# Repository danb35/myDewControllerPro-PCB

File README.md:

# myDewControllerPro-PCB
KiCad schematic and board for myDewControllerPro: https://sourceforge.net/projects/arduinonanodewcontrollerpro/

# Introduction
myFocuserPro is a DIY, Arduino-based dew heater controller designed for use with telescopes.  The design, source code, schematics, PCB files (Gerbers), and extensive documentation are available at the link above.  So what am I doing in this repo?

Unfortunately, the Gerbers there have a few issues, most notably that the footprint for the reverse-polarity protection diode (D1 on the schematic) just doesn't fit the specified diode.  The specified "fix" for the problem is to file down the leads of the diode until they fit through the holes.  And while this should be a trivial thing to fix, editable source files for the schematic and board haven't been released.

To address this, I re-drew the schematic and PCB layout in KiCad 6.0.  [KiCad](https://www.kicad.org/) is free, open source electronics design software, so you can download it to edit these files as desired.

# Design changes
This schematic is identical to the schematic at SourceForge.  I intend (and hope) that the schematic will be easier to read and follow, but there should not be any changes in the components or how they're connected.  Most of the reference designators (i.e., R3, C2, etc.) are identical, but KiCad has changed some of the semiconductors.  I have, however, made a few changes to the board layout.

First, of course, there's the change that drove the whole redesign--the footprint for D1 now actually fits the specified diode.  I've also replaced most of the places where pin headers had been used for off-board connections (e.g., for the pushbuttons, the display, etc.) with JST-XH connectors.  These provide some friction to prevent connections from coming loose inadvertently, and also polarize the connections (so, e.g., you can't plug in a LED backward).

# Bill of Materials
The bill of materials is not appreciably different from the upstream project, but it's now included in this repo, both as an OpenDocument Spreadsheet file and as a PDF.

# Enclosure
While the board size is similar to the original, it is not identical, and it will not fit in the 3D-printed case design that's posted on SourceForge.  I've designed an enclosure that will fit this board; STLs and STEP files are in the `Enclosure` directory.

# Board Images

# Ordering
I don't sell these boards; you can have them made by any PCB fab you choose.  To do so, simply download Gerber/myDewControllerPro.zip from this repo, upload it to your fab of choice, and have at it.  If you don't have a fab of choice, consider the two linked below, in which I have no financial interest (i.e., I'm not an affiliate, partner, or anything else; I don't make anything from your purchase of these boards--I'm just a customer of both services).

To order from JLCPCB, or most other PCB fabs, download the .zip file from the `Gerbers` directory.  You can then upload it to your preferred vendor to price and order your PCBs.

## OSHPark
OSHPark are an American company known for high-quality boards.  They'll produce three copies of your design for $5 per square inch, in purple, with gold plating.  This cost is often higher than the Chinese fabs, but they don't charge shipping, and you don't have to wait for shipping for China.  This board costs about $62 shipped for three copies as of this writing.  You can order boards using this link:
https://oshpark.com/profiles/danb35

## JLCPCB
[JLCPCB](https://jlcpcb.com/) are a Chinese PCB fab that I've been pretty happy with.  Their prices are low (starting at $2/5 boards), they produce the boards quickly, and they ship quickly via DHL.  The biggest drawback is the cost of shipping--at this writing, five boards will cost you $2, but the shipping is another $20 or more.

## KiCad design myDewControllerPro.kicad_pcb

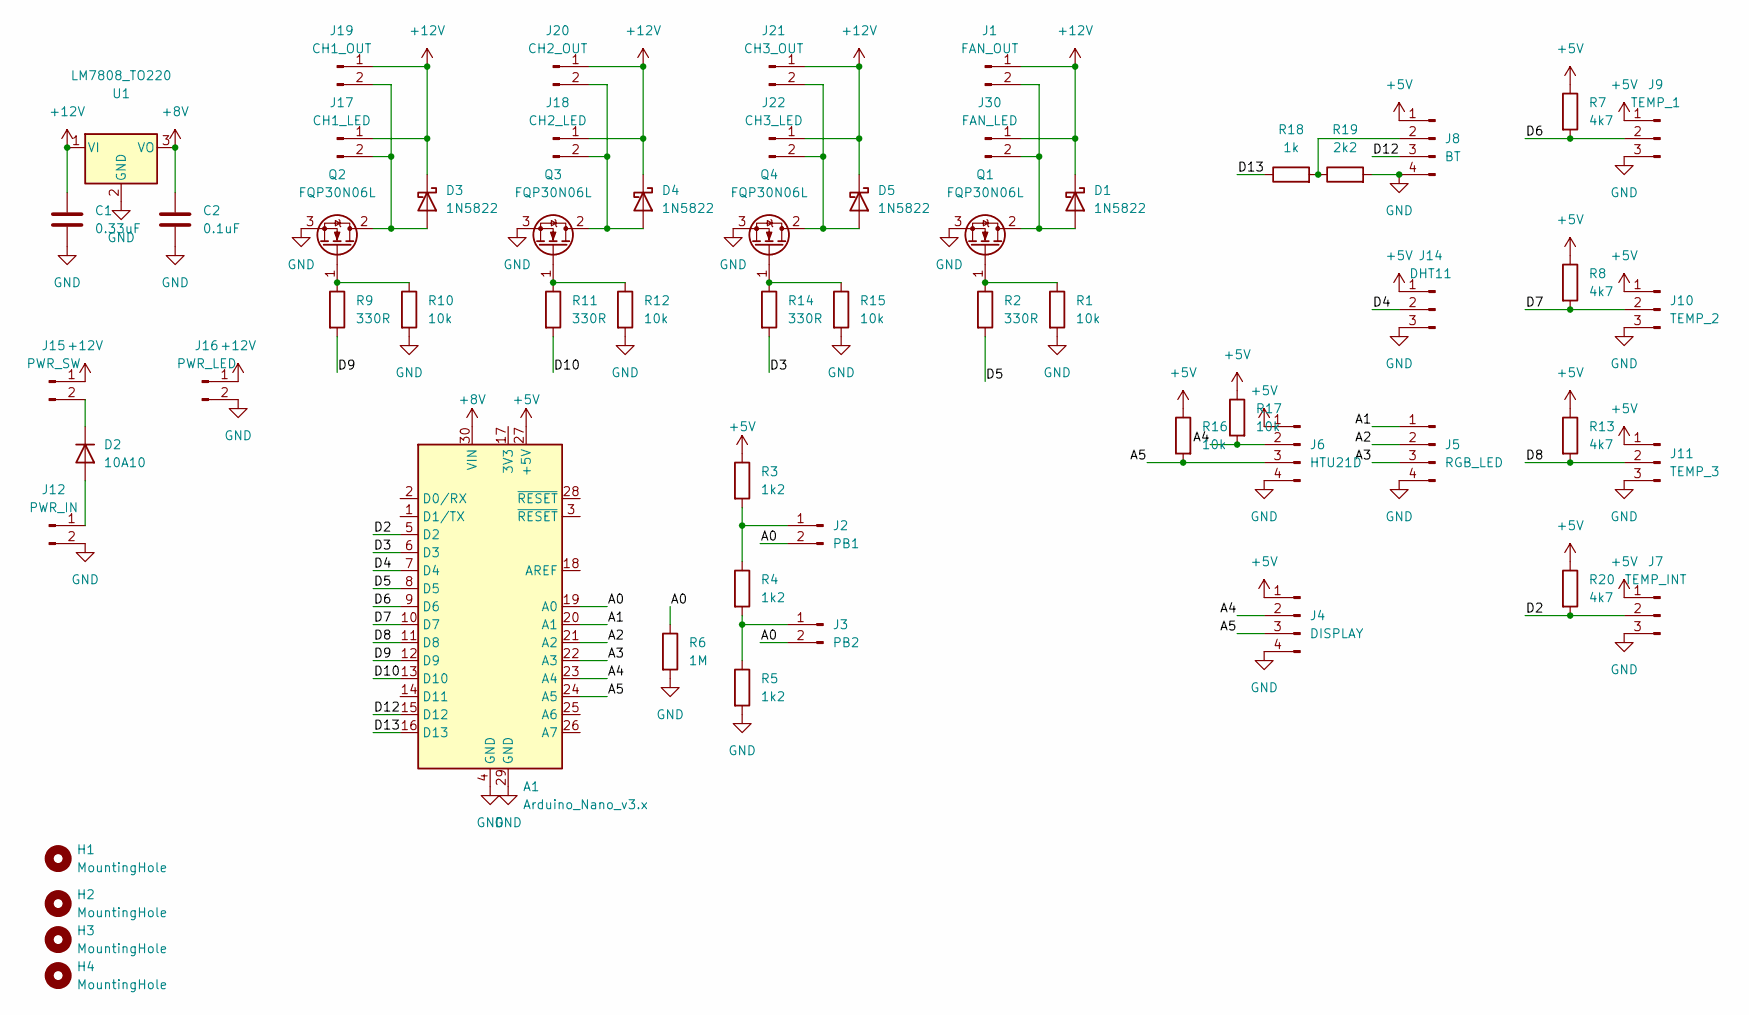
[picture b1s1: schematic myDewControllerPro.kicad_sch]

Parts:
A1: Arduino_Nano_v3.x; Arduino_Nano
C1: 0.33uF; C_Disc_D6.0mm_W4.4mm_P5.00mm
C2: 0.1uF; C_Disc_D6.0mm_W4.4mm_P5.00mm
D1, D3, D4, D5: 1N5822; D_DO-201AD_P15.24mm_Horizontal
D2: 10A10
H1, H2, H3, H4: MountingHole; MountingHole_3.2mm_M3
J1: FAN_OUT; JST_XH_B2B-XH-A_1x02_P2.50mm_Vertical
J2: PB1; JST_XH_B2B-XH-A_1x02_P2.50mm_Vertical
J3: PB2; JST_XH_B2B-XH-A_1x02_P2.50mm_Vertical
J4: DISPLAY; JST_XH_B4B-XH-A_1x04_P2.50mm_Vertical
J5: RGB_LED; JST_XH_B4B-XH-A_1x04_P2.50mm_Vertical
J6: HTU21D; JST_XH_B4B-XH-A_1x04_P2.50mm_Vertical
J7: TEMP_INT; JST_XH_B3B-XH-A_1x03_P2.50mm_Vertical
J8: BT; PinHeader_1x04_P2.54mm_Vertical
J9: TEMP_1; JST_XH_B3B-XH-A_1x03_P2.50mm_Vertical
J10: TEMP_2; JST_XH_B3B-XH-A_1x03_P2.50mm_Vertical
J11: TEMP_3; JST_XH_B3B-XH-A_1x03_P2.50mm_Vertical
J12: PWR_IN; JST_XH_B2B-XH-A_1x02_P2.50mm_Vertical
J14: DHT11; JST_XH_B3B-XH-AM_1x03_P2.50mm_Vertical
J15: PWR_SW; JST_XH_B2B-XH-A_1x02_P2.50mm_Vertical
J16: PWR_LED; JST_XH_B2B-XH-A_1x02_P2.50mm_Vertical
J17: CH1_LED; JST_XH_B2B-XH-A_1x02_P2.50mm_Vertical
J18: CH2_LED; JST_XH_B2B-XH-A_1x02_P2.50mm_Vertical
J19: CH1_OUT; JST_XH_B2B-XH-A_1x02_P2.50mm_Vertical
J20: CH2_OUT; JST_XH_B2B-XH-A_1x02_P2.50mm_Vertical
J21: CH3_OUT; JST_XH_B2B-XH-A_1x02_P2.50mm_Vertical
J22: CH3_LED; JST_XH_B2B-XH-A_1x02_P2.50mm_Vertical
J30: FAN_LED; JST_XH_B2B-XH-A_1x02_P2.50mm_Vertical
Q1, Q2, Q3, Q4: FQP30N06L; TO-220-3_Vertical
R1, R10, R12, R15, R16, R17: 10k; R_Axial_DIN0309_L9.0mm_D3.2mm_P5.08mm_Vertical
R2, R9, R11, R14: 330R; R_Axial_DIN0309_L9.0mm_D3.2mm_P5.08mm_Vertical
R3, R4, R5: 1k2; R_Axial_DIN0309_L9.0mm_D3.2mm_P5.08mm_Vertical
R6: 1M; R_Axial_DIN0309_L9.0mm_D3.2mm_P5.08mm_Vertical
R7, R8, R13, R20: 4k7; R_Axial_DIN0309_L9.0mm_D3.2mm_P5.08mm_Vertical
R18: 1k; R_Axial_DIN0309_L9.0mm_D3.2mm_P5.08mm_Vertical
R19: 2k2; R_Axial_DIN0309_L9.0mm_D3.2mm_P5.08mm_Vertical
U1: LM7808_TO220; TO-220-3_Vertical

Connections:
+5V: A1.27 (+5V), J4.1, J6.1, J7.1, J8.1, J9.1, J10.1, J11.1, J14.1, R3.1, R7.1, R8.1, R13.1, R16.1, R17.1, R20.1
+8V: A1.30 (VIN), C2.1, U1.3 (VO)
+12V: C1.1, D1.1 (K), D3.1 (K), D4.1 (K), D5.1 (K), J1.1, J15.1, J16.1, J17.1, J18.1, J19.1, J20.1, J21.1, J22.1, J30.1, U1.1 (VI)
/A0: A1.19 (A0), J2.2, J3.2, R6.1
/A1: A1.20 (A1), J5.1
/A2: A1.21 (A2), J5.2
/A3: A1.22 (A3), J5.3
/A4: A1.23 (A4), J4.2, J6.2, R17.2
/A5: A1.24 (A5), J4.3, J6.3, R16.2
/D2: A1.5 (D2), J7.2, R20.2
/D3: A1.6 (D3), R14.2
/D4: A1.7 (D4), J14.2
/D5: A1.8 (D5), R2.2
/D6: A1.9 (D6), J9.2, R7.2
/D7: A1.10 (D7), J10.2, R8.2
/D8: A1.11 (D8), J11.2, R13.2
/D9: A1.12 (D9), R9.2
/D10: A1.13 (D10), R11.2
/D12: A1.15 (D12), J8.3
/D13: A1.16 (D13), R18.1
GND: A1.4 (GND), A1.29 (GND), C1.2, C2.2, J4.4, J5.4, J6.4, J7.3, J8.4, J9.3, J10.3, J11.3, J12.2, J14.3, J16.2, Q1.3 (S), Q2.3 (S), Q3.3 (S), Q4.3 (S), R1.2, R5.2, R6.2, R10.2, R12.2, R15.2, R19.2, U1.2 (GND)
unnamed: D1.2 (A), J1.2, J30.2, Q1.2 (D)
unnamed: D2.1 (K), J15.2
unnamed: D2.2 (A), J12.1
unnamed: D3.2 (A), J17.2, J19.2, Q2.2 (D)
unnamed: D4.2 (A), J18.2, J20.2, Q3.2 (D)
unnamed: D5.2 (A), J21.2, J22.2, Q4.2 (D)
unnamed: J2.1, R3.2, R4.1
unnamed: J3.1, R4.2, R5.1
unnamed: J8.2, R18.2, R19.1
unnamed: Q1.1 (G), R1.1, R2.1
unnamed: Q2.1 (G), R9.1, R10.1
unnamed: Q3.1 (G), R11.1, R12.1
unnamed: Q4.1 (G), R14.1, R15.1

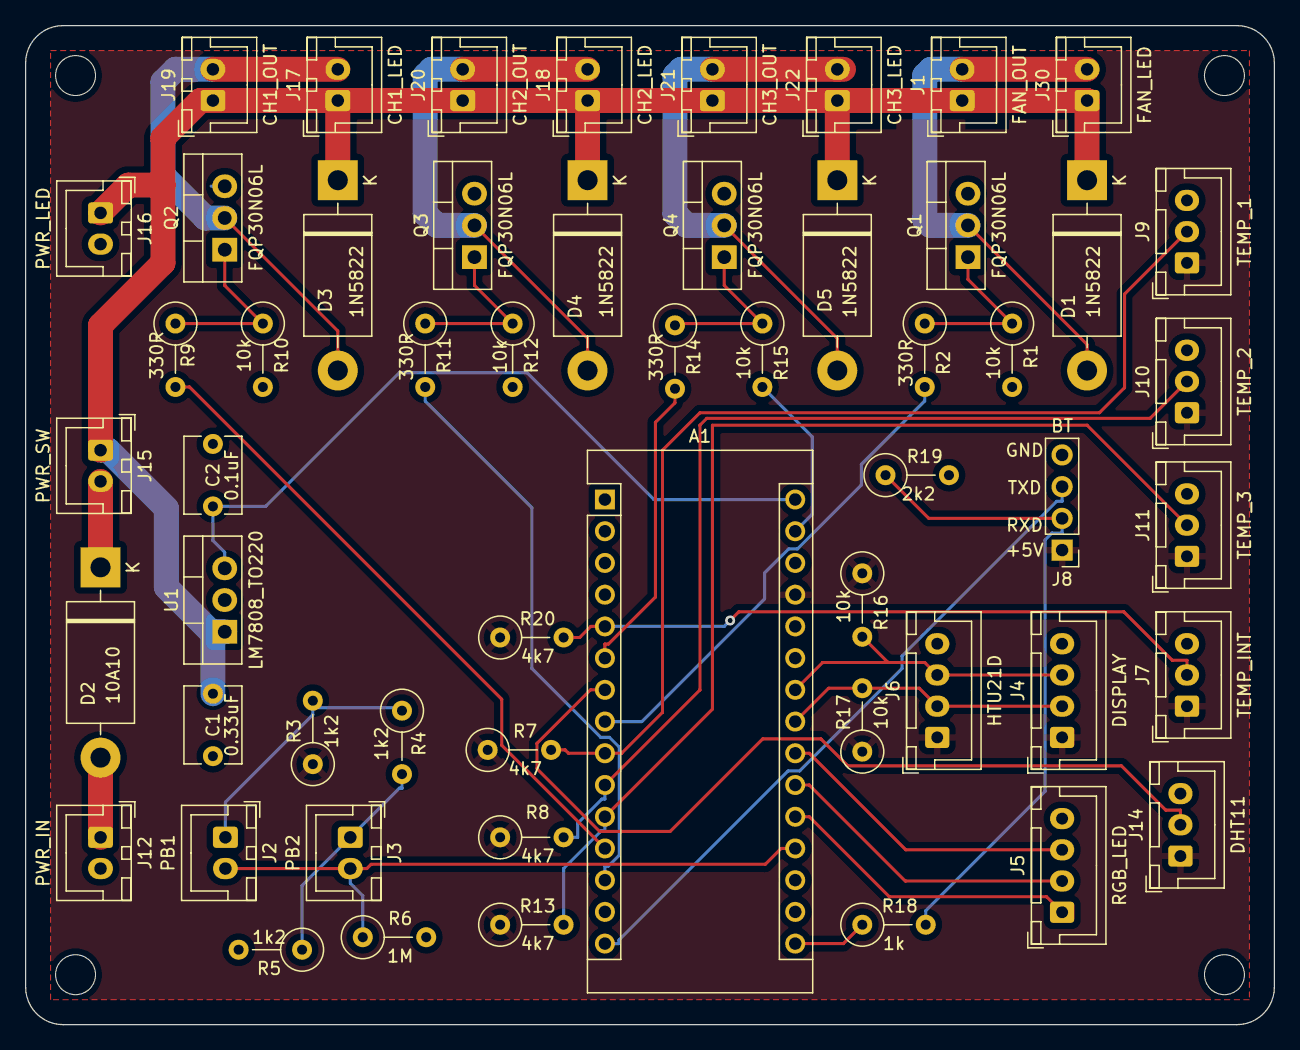
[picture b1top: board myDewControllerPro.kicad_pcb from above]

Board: 2 copper layers, 100.0 x 80.0 mm, 59 parts (0 on the bottom side), 34 nets.

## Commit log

2022-04-29 Add enclosure
2022-04-29 Add BOM
2022-04-30 Update BOM
    PDF now in landscape
